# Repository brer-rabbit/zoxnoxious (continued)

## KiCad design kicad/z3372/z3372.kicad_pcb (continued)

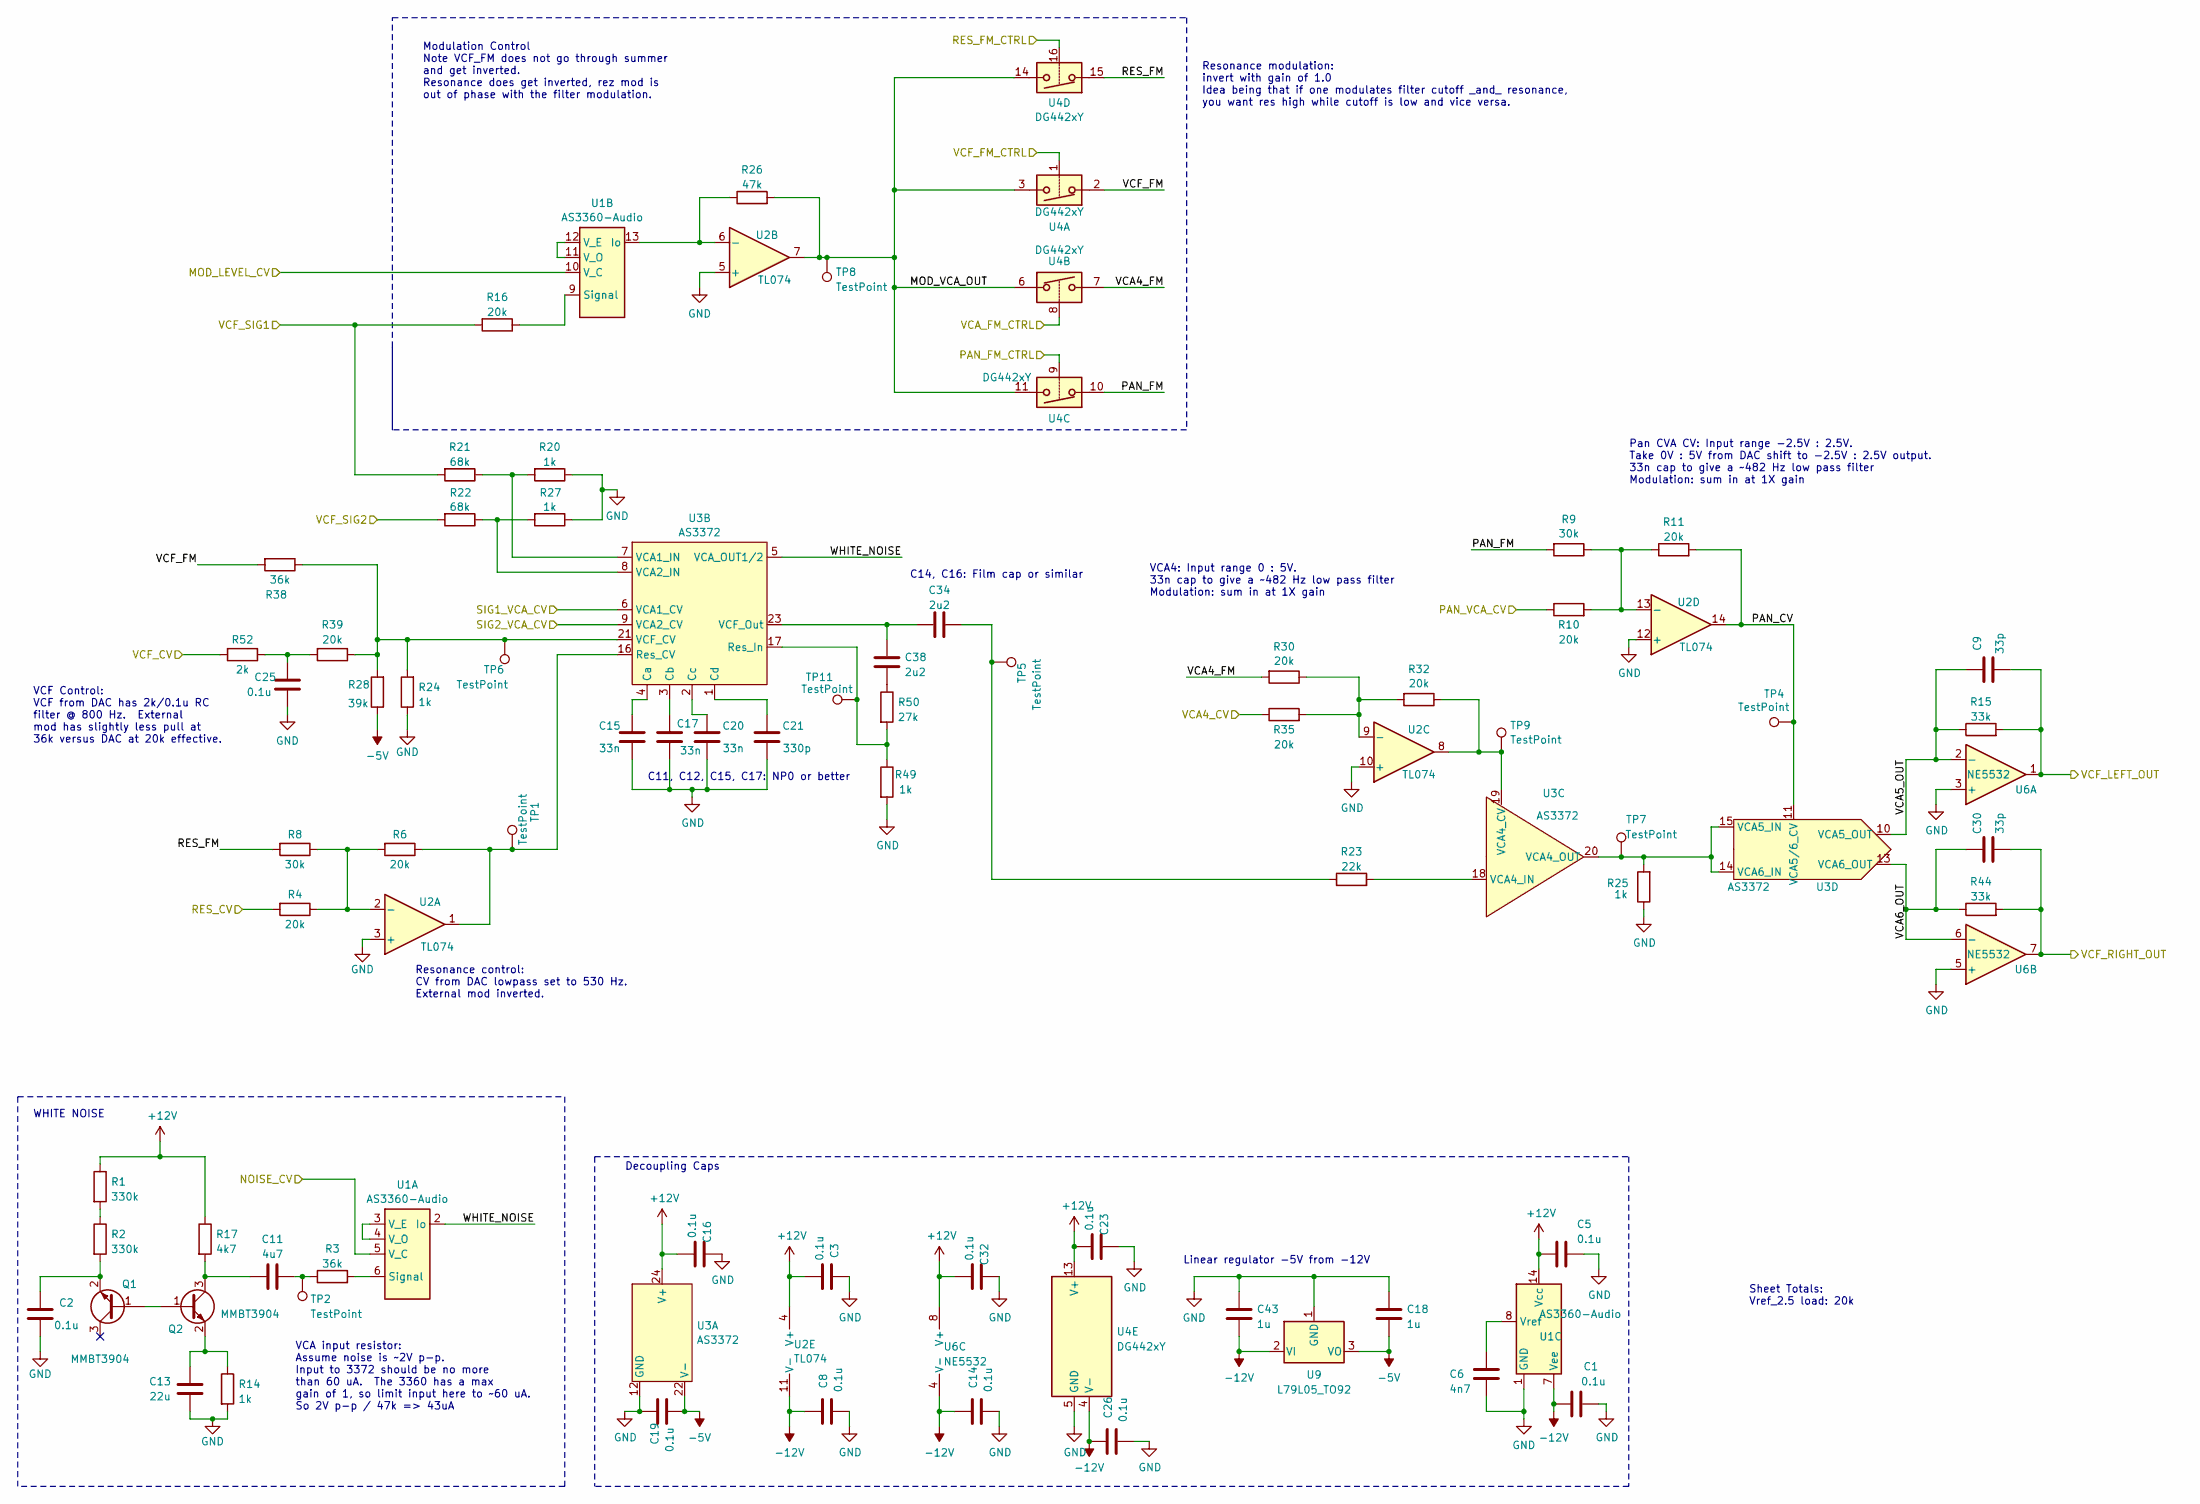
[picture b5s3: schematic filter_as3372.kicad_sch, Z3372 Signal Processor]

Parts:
C1, C2, C3, C5, C8, C14, C16, C19, C23, C25, C26, C32: 0.1u; C_0603_1608Metric; LCSC C14663
C6: 4n7; C_0603_1608Metric; LCSC C53987
C9, C30: 33p; C_0603_1608Metric; LCSC C1663
C11: 4u7; C_0805_2012Metric; LCSC C1779
C13: 22u; C_1206_3216Metric; LCSC C12891
C15, C17, C20: 33n; C_0805_2012Metric; LCSC C76628
C18, C43: 1u; C_0805_2012Metric; LCSC C28323
C21: 330p; C_0603_1608Metric; LCSC C1664
C34, C38: 2u2; C_Rect_L7.2mm_W5.5mm_P5.00mm_FKS2_FKP2_MKS2_MKP2; Digikey MKS2B042201F00KSSD
Q1, Q2: MMBT3904; SOT-23; LCSC C20526
R1, R2: 330k; R_0603_1608Metric; LCSC C23137
R3, R38: 36k; R_0603_1608Metric; LCSC C23147
R4, R6, R10, R11, R16, R30, R32, R35, R39: 20k; R_0603_1608Metric; LCSC C4184
R8, R9: 30k; R_0603_1608Metric; LCSC C22984
R14, R20, R24, R25, R27, R49: 1k; R_0603_1608Metric; LCSC C21190
R15, R44: 33k; R_0603_1608Metric; LCSC C4216
R17: 4k7; R_0603_1608Metric; LCSC C23162
R21, R22: 68k; R_0603_1608Metric; LCSC C23231
R23: 22k; R_0603_1608Metric; LCSC C31850
R26: 47k; R_0603_1608Metric; LCSC C25819
R28: 39k; R_0603_1608Metric; LCSC C23153
R50: 27k; R_0603_1608Metric; LCSC C22967
R52: 2k; R_0603_1608Metric; LCSC C22975
TP1, TP2, TP4, TP5, TP6, TP7, TP8, TP9, TP11: TestPoint; TestPoint_Pad_2.0x2.0mm
U1: AS3360-Audio; SOIC-14_3.9x8.7mm_P1.27mm
U2: TL074; TSSOP-14_4.4x5mm_P0.65mm; LCSC C96507
U3: AS3372; SOIC-24W_7.5x15.4mm_P1.27mm
U4: DG442xY; SOIC-16_3.9x9.9mm_P1.27mm; LCSC C2673321
U6: NE5532; SOIC-8_3.9x4.9mm_P1.27mm; LCSC C7426
U9: L79L05_TO92; TO-92_Inline_Wide

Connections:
+12V: C3.2, C5.2, C16.2, C23.2, C32.2, R1.1, R17.1, U1.14 (Vcc), U2.4 (V+), U3.24 (V+), U4.13 (V+), U6.8 (V+); also elsewhere on the board
-5V: C18.2, C19.2, R28.1, U3.22 (V-), U9.3 (VO)
-12V: C1.1, C8.1, C14.1, C26.1, C43.2, U1.7 (Vee), U2.11 (V-), U4.4 (V-), U6.4 (V-), U9.2 (VI); also elsewhere on the board
/DAC/FINAL_VCA4_CV: R35.1; also elsewhere on the board
/DAC/MOD_AMOUNT_CV: U1.10 (V_C); also elsewhere on the board
/DAC/NOISE_CONTROL_CV: U1.5 (V_C); also elsewhere on the board
/DAC/PAN_VCA_CV: R10.1; also elsewhere on the board
/DAC/RESONANCE_CV: R4.2; also elsewhere on the board
/DAC/SIG1_VCA1_CV: U3.6 (VCA1_CV); also elsewhere on the board
/DAC/SIG2_VCA2_CV: U3.9 (VCA2_CV); also elsewhere on the board
/DAC/VCF_CV: R52.2; also elsewhere on the board
/PAN_FM_CTRL: U4.9; also elsewhere on the board
/RES_FM_CTRL: U4.16; also elsewhere on the board
/VCA_FM_CTRL: U4.8; also elsewhere on the board
/VCF_FM_CTRL: U4.1; also elsewhere on the board
/VCF_LEFT: C9.2, R15.2, U6.1; also elsewhere on the board
/VCF_SIGNAL1: R16.2, R21.2; also elsewhere on the board
/VCF_SIGNAL2: R22.2; also elsewhere on the board
/filter_as3372/MOD_VCA_OUT: R26.2, TP8.1, U2.7, U4.3, U4.6, U4.11, U4.14
/filter_as3372/PAN_CV: R11.2, TP4.1, U2.14, U3.11 (VCA5/6_CV)
/filter_as3372/PAN_FM: R9.2, U4.10
/filter_as3372/RES_FM: R8.2, U4.15
/filter_as3372/VCA4_FM: R30.2, U4.7
/filter_as3372/VCA5_OUT: C9.1, R15.1, U3.10 (VCA5_OUT), U6.2 (-)
/filter_as3372/VCA6_OUT: C30.1, R44.1, U3.13 (VCA6_OUT), U6.6 (-)
/filter_as3372/VCF_FM: R38.2, U4.2
/filter_as3372/VCF_RIGHT_OUT: C30.2, R44.2, U6.7; also elsewhere on the board
/filter_as3372/WHITE_NOISE: U1.2 (Io), U3.5 (VCA_OUT1/2)
GND: C1.2, C2.2, C3.1, C5.1, C6.2, C8.2, C13.2, C14.2, C15.1, C16.1, C17.2, C18.1, C19.1, C20.2, C21.2, C23.1, C25.2, C26.2, C32.1, C43.1, R14.2, R20.1, R24.1, R25.1, R27.1, R49.2, U1.1 (GND), U2.3 (+), U2.5 (+), U2.10 (+), U2.12 (+), U3.12 (GND), U4.5 (GND), U6.3 (+), U6.5 (+), U9.1 (GND); also elsewhere on the board
unnamed: C11.2, R3.1, TP2.1
unnamed: C25.1, R39.2, R52.1
unnamed: C34.2, R23.1, TP5.1
unnamed: C38.2, R50.1
unnamed: Q1.1 (B), Q2.1 (B)
unnamed: C2.1, Q1.2 (E), R2.2
unnamed: C11.1, Q2.3 (C), R17.2
unnamed: C13.1, Q2.2 (E), R14.1
unnamed: R1.2, R2.1
unnamed: R3.2, U1.6 (Signal)
unnamed: U1.3 (V_E), U1.4 (V_O)
unnamed: R26.1, U1.13 (Io), U2.6 (-)
unnamed: R16.1, U1.9 (Signal)
unnamed: U1.11 (V_O), U1.12 (V_E)
unnamed: C6.1, U1.8 (Vref)
unnamed: R4.1, R6.2, R8.1, U2.2 (-)
unnamed: R30.1, R32.2, R35.2, U2.9 (-)
unnamed: R9.1, R10.2, R11.1, U2.13 (-)
unnamed: C15.2, U3.4 (Ca)
unnamed: C17.1, U3.3 (Cb)
unnamed: C20.1, U3.2 (Cc)
unnamed: C21.1, U3.1 (Cd)
unnamed: R6.1, TP1.1, U2.1, U3.16 (Res_CV)
unnamed: R49.1, R50.2, TP11.1, U3.17 (Res_In)
unnamed: R20.2, R21.1, U3.7 (VCA1_IN)
unnamed: R22.1, R27.2, U3.8 (VCA2_IN)
unnamed: R24.2, R28.2, R38.1, R39.1, TP6.1, U3.21 (VCF_CV)
unnamed: C34.1, C38.1, U3.23 (VCF_Out)
unnamed: R32.1, TP9.1, U2.8, U3.19 (VCA4_CV)
unnamed: R23.2, U3.18 (VCA4_IN)
unnamed: R25.2, TP7.1, U3.14 (VCA6_IN), U3.15 (VCA5_IN), U3.20 (VCA4_OUT)

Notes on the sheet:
Modulation Control Note VCF_FM does not go through summer and get inverted. Resonance does get inverted, rez mod is out of phase with the filter modulation.
Resonance modulation: invert with gain of 1.0 Idea being that if one modulates filter cutoff _and_ resonance, you want res high while cutoff is low and vice versa.
Resonance control: CV from DAC lowpass set to 530 Hz. External mod inverted.
VCA4: Input range 0 : 5V. 33n cap to give a ~482 Hz low pass filter Modulation: sum in at 1X gain
Decoupling Caps
C14, C16: Film cap or similar
VCF Control: VCF from DAC has 2k/0.1u RC filter @ 800 Hz. External mod has slightly less pull at 36k versus DAC at 20k effective.
WHITE NOISE
Pan CVA CV: Input range -2.5V : 2.5V. Take 0V : 5V from DAC shift to -2.5V : 2.5V output. 33n cap to give a ~482 Hz low pass filter Modulation: sum in at 1X gain
Sheet Totals: Vref_2.5 load: 20k
Linear regulator -5V from -12V
C11, C12, C15, C17: NP0 or better
VCA input resistor: Assume noise is ~2V p-p. Input to 3372 should be no more than 60 uA. The 3360 has a max gain of 1, so limit input here to ~60 uA. So 2V p-p / 47k => 43uA

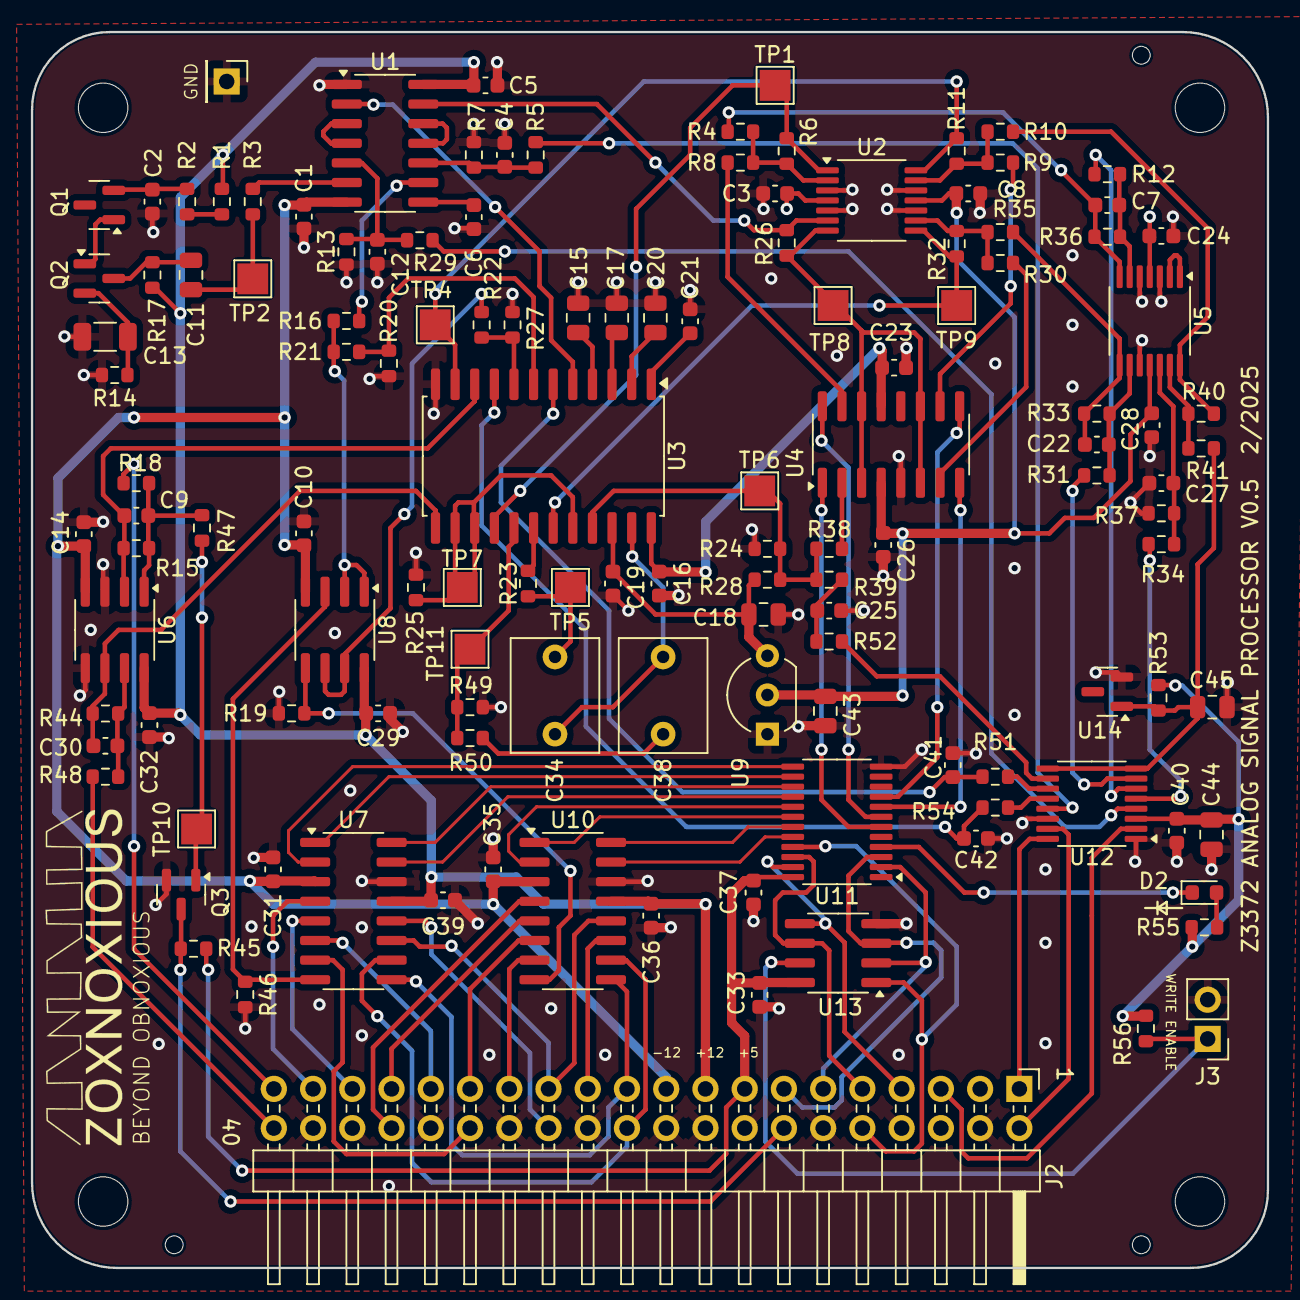
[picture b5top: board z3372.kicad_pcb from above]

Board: 4 copper layers, 80.0 x 80.0 mm, 134 parts (0 on the bottom side), 112 nets.

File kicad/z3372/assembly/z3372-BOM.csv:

Comment,Designator,Footprint,LCSC Part #
"0.1u","C1,C2,C3,C4,C5,C8,C10,C12,C14,C16,C19,C23,C24,C25,C26,C28,C29,C31,C32,C33,C35,C36,C37,C39,C40","Capacitor_SMD:C_0603_1608Metric","C14663"
"22u","C13","Capacitor_SMD:C_1206_3216Metric","C12891"
"33n","C15,C17,C20","Capacitor_SMD:C_0805_2012Metric","C76628"
"330p","C21","Capacitor_SMD:C_0603_1608Metric","C1664"
"22n","C22","Capacitor_SMD:C_0603_1608Metric","C21122"
"47n","C27","Capacitor_SMD:C_0603_1608Metric","C1622"
"4u7","C11,C44","Capacitor_SMD:C_0805_2012Metric","C1779"
"1u","C18,C43,C45","Capacitor_SMD:C_0805_2012Metric","C28323"
"4n7","C6","Capacitor_SMD:C_0603_1608Metric","C53987"
"10n","C7,C41,C42","Capacitor_SMD:C_0603_1608Metric","C57112"
"33p","C9,C30","Capacitor_SMD:C_0603_1608Metric","C1663"
"LED","D2","LED_SMD:LED_0603_1608Metric","C2286"
"MMBT3904","Q1,Q2,Q3","Package_TO_SOT_SMD:SOT-23","C20526"
"330k","R1,R2","Resistor_SMD:R_0603_1608Metric","C23137"
"47k","R12,R26","Resistor_SMD:R_0603_1608Metric","C25819"
"1k","R14,R20,R24,R25,R27,R49","Resistor_SMD:R_0603_1608Metric","C21190"
"51","R18,R48","Resistor_SMD:R_0603_1608Metric","C23197"
"100k","R19,R46,R47","Resistor_SMD:R_0603_1608Metric","C25803"
"68k","R21,R22","Resistor_SMD:R_0603_1608Metric","C23231"
"22k","R23","Resistor_SMD:R_0603_1608Metric","C31850"
"39k","R28","Resistor_SMD:R_0603_1608Metric","C23153"
"36k","R3,R38","Resistor_SMD:R_0603_1608Metric","C23147"
"20k","R4,R6,R10,R11,R16,R30,R31,R32,R33,R34,R35,R37,R39,R40,R41","Resistor_SMD:R_0603_1608Metric","C4184"
"33k","R15,R36,R44","Resistor_SMD:R_0603_1608Metric","C4216"
"10k","R45","Resistor_SMD:R_0603_1608Metric","C25804"
"15k","R5,R29,R51,R54","Resistor_SMD:R_0603_1608Metric","C22809"
"27k","R50","Resistor_SMD:R_0603_1608Metric","C22967"
"2k","R52","Resistor_SMD:R_0603_1608Metric","C22975"
"4k7","R17,R53,R55,R56","Resistor_SMD:R_0603_1608Metric","C23162"
"9k1","R7,R13","Resistor_SMD:R_0603_1608Metric","C23260"
"30k","R8,R9","Resistor_SMD:R_0603_1608Metric","C22984"
"CAT9555YI-T2","U11","Package_SO:TSSOP-24_4.4x7.8mm_P0.65mm","C83265"
"AD5328","U12","Package_SO:TSSOP-16_4.4x5mm_P0.65mm","C29162"
"M24C02-WMN","U13","Package_SO:SOIC-8_3.9x4.9mm_P1.27mm","C7562"
"LM4040AIM3-2.5","U14","Package_TO_SOT_SMD:SOT-23","C460725"
"DG442xY","U4","Package_SO:SOIC-16_3.9x9.9mm_P1.27mm","C2673321"
"TL074","U2,U5","Package_SO:TSSOP-14_4.4x5mm_P0.65mm","C96507"
"NE5532","U6","Package_SO:SOIC-8_3.9x4.9mm_P1.27mm","C7426"
"MUX508","U7,U10","Package_SO:SOIC-16_3.9x9.9mm_P1.27mm","C2673104"
"TL072","U8","Package_SO:SOIC-8_3.9x4.9mm_P1.27mm","C6961"

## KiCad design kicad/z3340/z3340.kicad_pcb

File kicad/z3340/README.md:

# Z3340 Voltage Controlled Oscillator

The Z3340 VCO is based around Alfa Rpar's AS3340 clone of the Curtis chip.  This design, like other Zoxnoxious designs, interfaces with the Zoxnoxious signal bus.

# Block Diagram

# Resources

[Datasheet](datasheet_3340.pdf)

[Kicanvas](https://kicanvas.org/?github=https%3A%2F%2Fgithub.com%2Fbrer-rabbit%2Fzoxnoxious%2Ftree%2Fmain%2Fkicad%2Fz3340)

# Demo

YouTube Demo

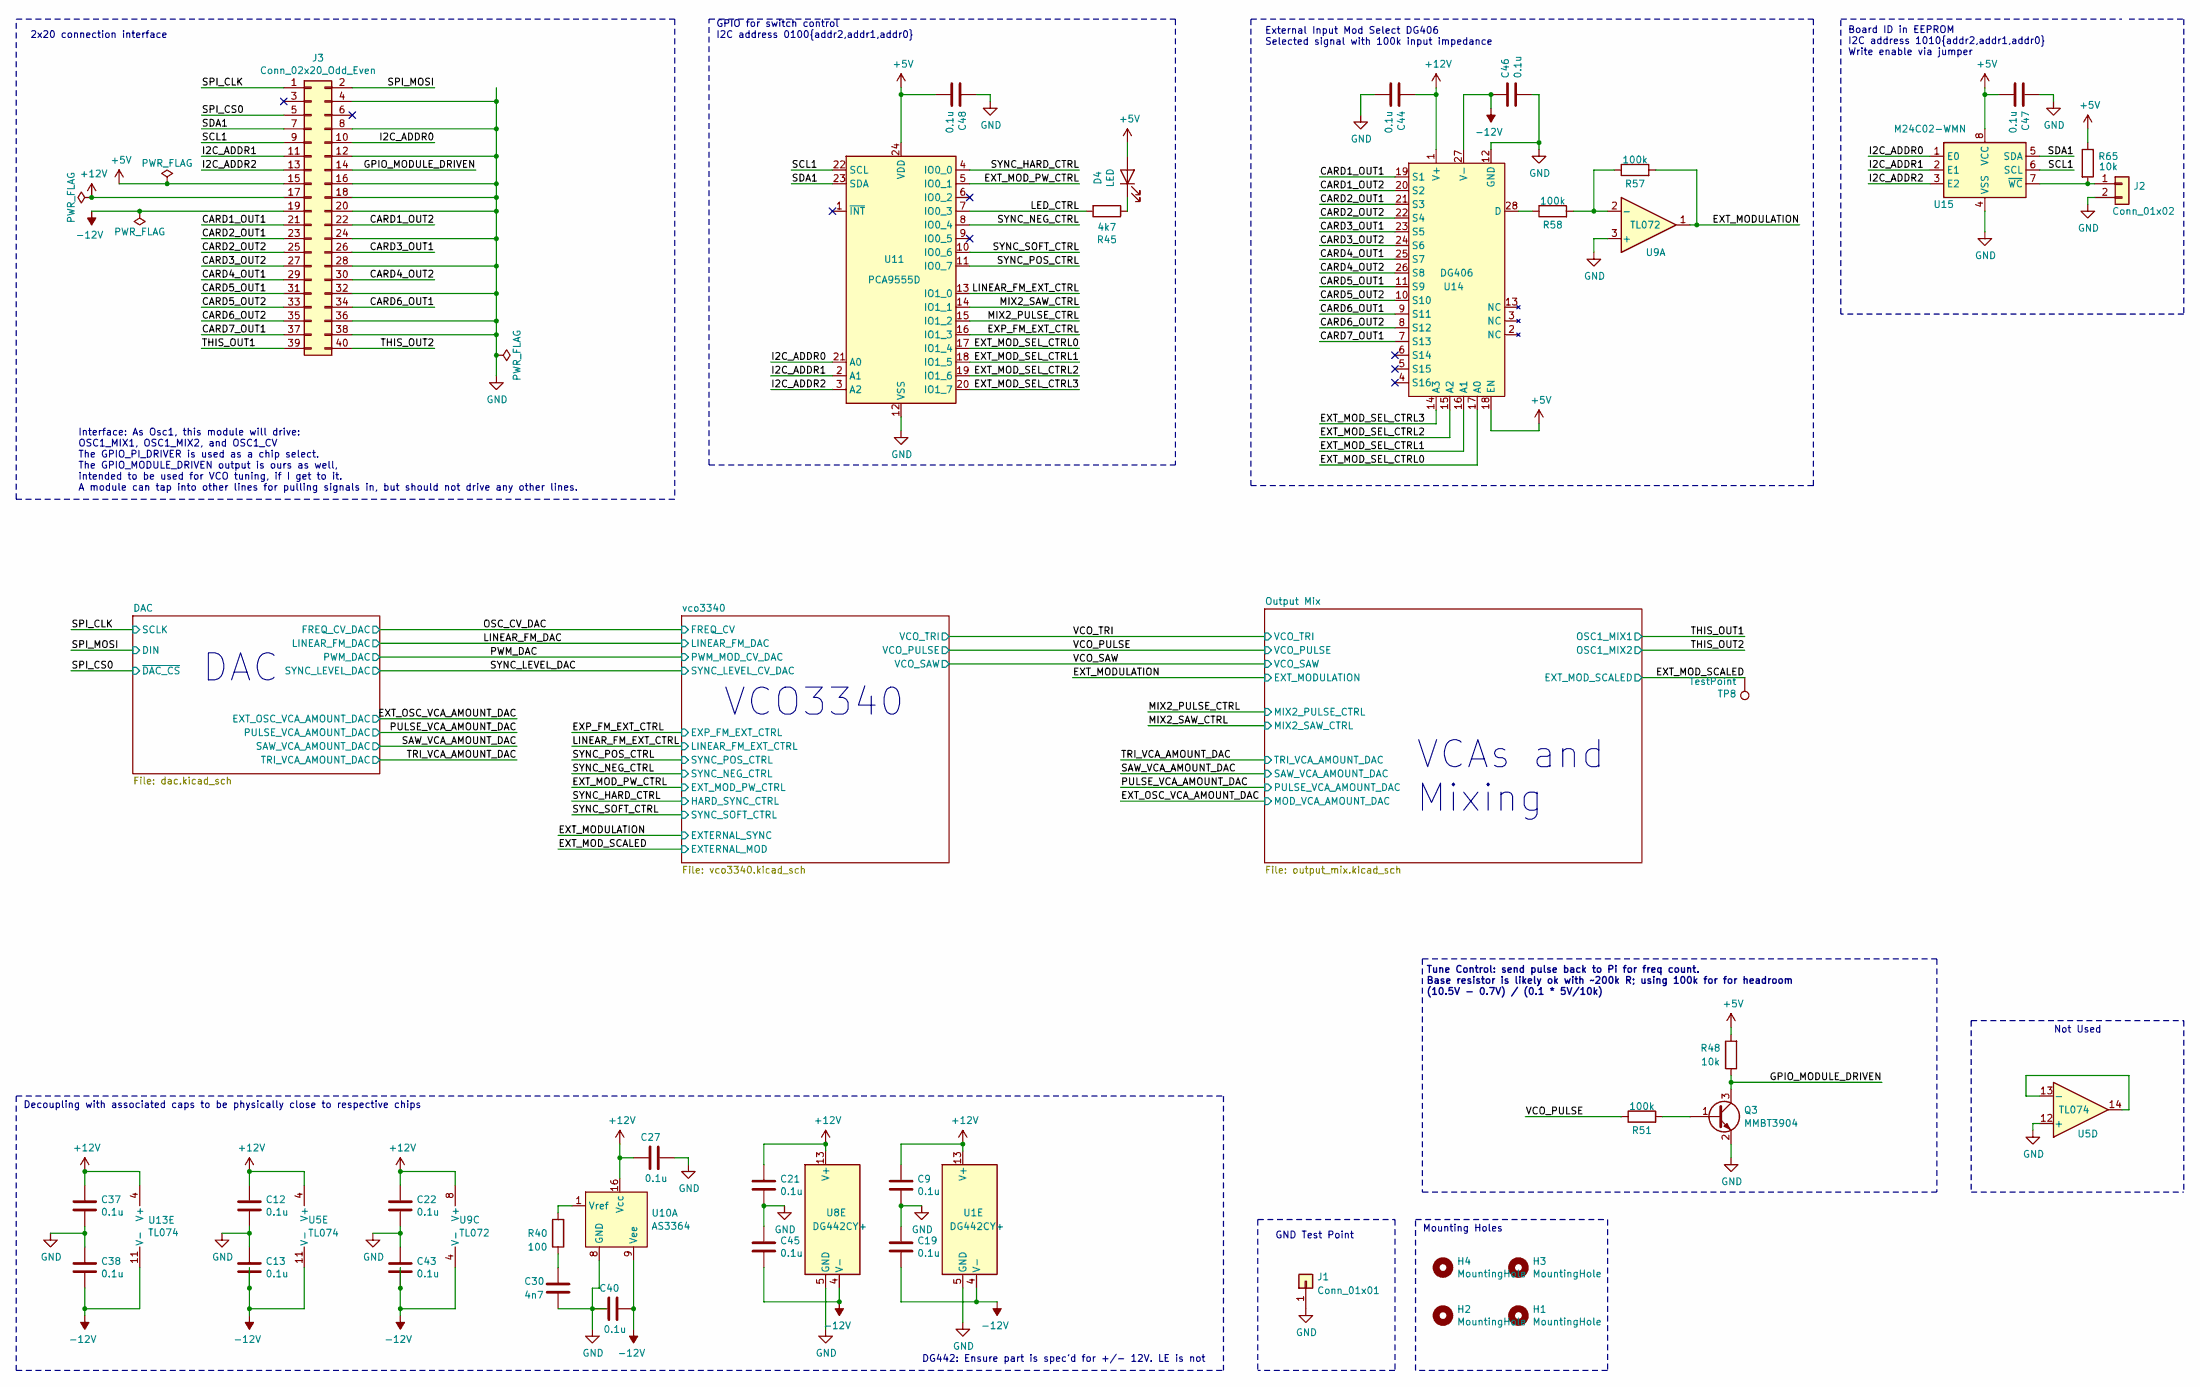
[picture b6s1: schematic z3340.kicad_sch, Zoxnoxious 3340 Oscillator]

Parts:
C9, C12, C13, C19, C21, C22, C27, C37, C38, C40, C43, C44, C45, C46, C47, C48: 0.1u; C_0603_1608Metric; LCSC C14663
C30: 4n7; C_0603_1608Metric; LCSC C53987
D4: LED; LED_0603_1608Metric; LCSC C2286
H1, H2, H3, H4: MountingHole; MountingHole_3.2mm_M3
J1: Conn_01x01; PinHeader_1x01_P2.54mm_Vertical
J2: Conn_01x02; PinHeader_1x02_P2.54mm_Vertical
J3: Conn_02x20_Odd_Even; PinHeader_2x20_P2.54mm_Horizontal
Q3: MMBT3904; SOT-23; LCSC C20526
R40: 100; R_0603_1608Metric; LCSC C22775
R45: 4k7; R_0603_1608Metric; LCSC C23162
R48, R65: 10k; R_0603_1608Metric; LCSC C25804
R51, R57, R58: 100k; R_0603_1608Metric; LCSC C25803
TP8: TestPoint; TestPoint_Pad_2.0x2.0mm; Digikey 952-2664-6-ND
U1, U8: DG442CY+; SOIC-16_3.9x9.9mm_P1.27mm; Digikey DG442CY+-ND
U5, U13: TL074; TSSOP-14_4.4x5mm_P0.65mm; LCSC C96507
U9: TL072; SSOP-8_3.9x5.05mm_P1.27mm; LCSC C6961
U10: AS3364; SOIC-16_3.9x9.9mm_P1.27mm
U11: PCA9555D; TSSOP-24_4.4x7.8mm_P0.65mm; LCSC C83265
U14: DG406; SOIC-28W_7.5x17.9mm_P1.27mm; LCSC C426318
U15: M24C02-WMN; SOIC-8_3.9x4.9mm_P1.27mm; LCSC C7562

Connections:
+5V: C47.2, C48.2, D4.2 (A), J3.15, R48.2, R65.1, U11.24 (VDD), U14.18 (EN), U15.8 (VCC); also elsewhere on the board
+12V: C9.1, C12.1, C21.1, C22.1, C27.1, C37.1, C44.1, J3.17, U1.13 (V+), U5.4 (V+), U8.13 (V+), U9.8 (V+), U10.16 (Vcc), U13.4 (V+), U14.1 (V+); also elsewhere on the board
-12V: C13.2, C19.2, C38.2, C40.2, C43.2, C45.2, C46.1, J3.19, U1.4 (V-), U5.11 (V-), U8.4 (V-), U9.4 (V-), U10.9 (Vee), U13.11 (V-), U14.27 (V-); also elsewhere on the board
/CARD1_OUT1: J3.21, U14.19 (S1)
/CARD1_OUT2: J3.22, U14.20 (S2)
/CARD2_OUT1: J3.23, U14.21 (S3)
/CARD2_OUT2: J3.25, U14.22 (S4)
/CARD3_OUT1: J3.26, U14.23 (S5)
/CARD3_OUT2: J3.27, U14.24 (S6)
/CARD4_OUT1: J3.29, U14.25 (S7)
/CARD4_OUT2: J3.30, U14.26 (S8)
/CARD5_OUT1: J3.31, U14.11 (S9)
/CARD5_OUT2: J3.33, U14.10 (S10)
/CARD6_OUT1: J3.34, U14.9 (S11)
/CARD6_OUT2: J3.35, U14.8 (S12)
/CARD7_OUT1: J3.37, U14.7 (S13)
/EXP_FM_EXT_CTRL: U11.16 (IO1_3); also elsewhere on the board
/EXT_MODULATION: R57.2, U9.1; also elsewhere on the board
/EXT_MOD_PW_CTRL: U11.5 (IO0_1); also elsewhere on the board
/EXT_MOD_SCALED: TP8.1; also elsewhere on the board
/EXT_MOD_SEL_CTRL0: U11.17 (IO1_4), U14.17 (A0)
/EXT_MOD_SEL_CTRL1: U11.18 (IO1_5), U14.16 (A1)
/EXT_MOD_SEL_CTRL2: U11.19 (IO1_6), U14.15 (A2)
/EXT_MOD_SEL_CTRL3: U11.20 (IO1_7), U14.14 (A3)
/GPIO_MODULE_DRIVEN: J3.14, Q3.3 (C), R48.1
/I2C_ADDR0: J3.10, U11.21 (A0), U15.1 (E0)
/I2C_ADDR1: J3.11, U11.2 (A1), U15.2 (E1)
/I2C_ADDR2: J3.13, U11.3 (A2), U15.3 (E2)
/LED_CTRL: R45.2, U11.7 (IO0_3)
/LINEAR_FM_EXT_CTRL: U11.13 (IO1_0); also elsewhere on the board
/MIX2_PULSE_CTRL: U11.15 (IO1_2); also elsewhere on the board
/MIX2_SAW_CTRL: U11.14 (IO1_1); also elsewhere on the board
/SCL1: J3.9, U11.22 (SCL), U15.6 (SCL)
/SDA1: J3.7, U11.23 (SDA), U15.5 (SDA)
/SPI_CLK: J3.1; also elsewhere on the board
/SPI_CS0: J3.5; also elsewhere on the board
/SPI_MOSI: J3.2; also elsewhere on the board
/SYNC_HARD_CTRL: U11.4 (IO0_0); also elsewhere on the board
/SYNC_NEG_CTRL: U11.8 (IO0_4); also elsewhere on the board
/SYNC_POS_CTRL: U11.11 (IO0_7); also elsewhere on the board
/SYNC_SOFT_CTRL: U11.10 (IO0_6); also elsewhere on the board
/THIS_OUT1: J3.39; also elsewhere on the board
/THIS_OUT2: J3.40; also elsewhere on the board
/VCO_PULSE: R51.1; also elsewhere on the board
GND: C9.2, C12.2, C13.1, C19.1, C21.2, C22.2, C27.2, C30.2, C37.2, C38.1, C40.1, C43.1, C44.2, C45.1, C46.2, C47.1, C48.1, J1.1, J2.2, J3.4, J3.8, J3.12, J3.16, J3.18, J3.20, J3.24, J3.28, J3.32, J3.36, J3.38, Q3.2 (E), U1.5 (GND), U5.12 (+), U8.5 (GND), U9.3 (+), U10.8 (GND), U11.12 (VSS), U14.12 (GND), U15.4 (VSS); also elsewhere on the board
unnamed: C30.1, R40.1
unnamed: D4.1 (K), R45.1
unnamed: J2.1, R65.2, U15.7 (~WC)
unnamed: Q3.1 (B), R51.2
unnamed: U5.13 (-), U5.14
unnamed: R57.1, R58.2, U9.2 (-)
unnamed: R40.2, U10.1 (Vref)
unnamed: R58.1, U14.28 (D)

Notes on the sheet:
Tune Control: send pulse back to Pi for freq count. Base resistor is likely ok with ~200k R; using 100k for for headroom (10.5V - 0.7V) / (0.1 * 5V/10k)
External Input Mod Select DG406 Selected signal with 100k input impedance
Decoupling with associated caps to be physically close to respective chips
DG442: Ensure part is spec’d for +/- 12V. LE is not
2x20 connection interface
VCO3340
VCAs and Mixing
GPIO for switch control I2C address 0100{addr2,addr1,addr0}
Not Used
Mounting Holes
GND Test Point
Board ID in EEPROM I2C address 1010{addr2,addr1,addr0} Write enable via jumper
Interface: As Osc1, this module will drive: OSC1_MIX1, OSC1_MIX2, and OSC1_CV The GPIO_PI_DRIVER is used as a chip select. The GPIO_MODULE_DRIVEN output is ours as well, intended to be used for VCO tuning, if I get to it. A module can tap into other lines for pulling signals in, but should not driv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
DAC

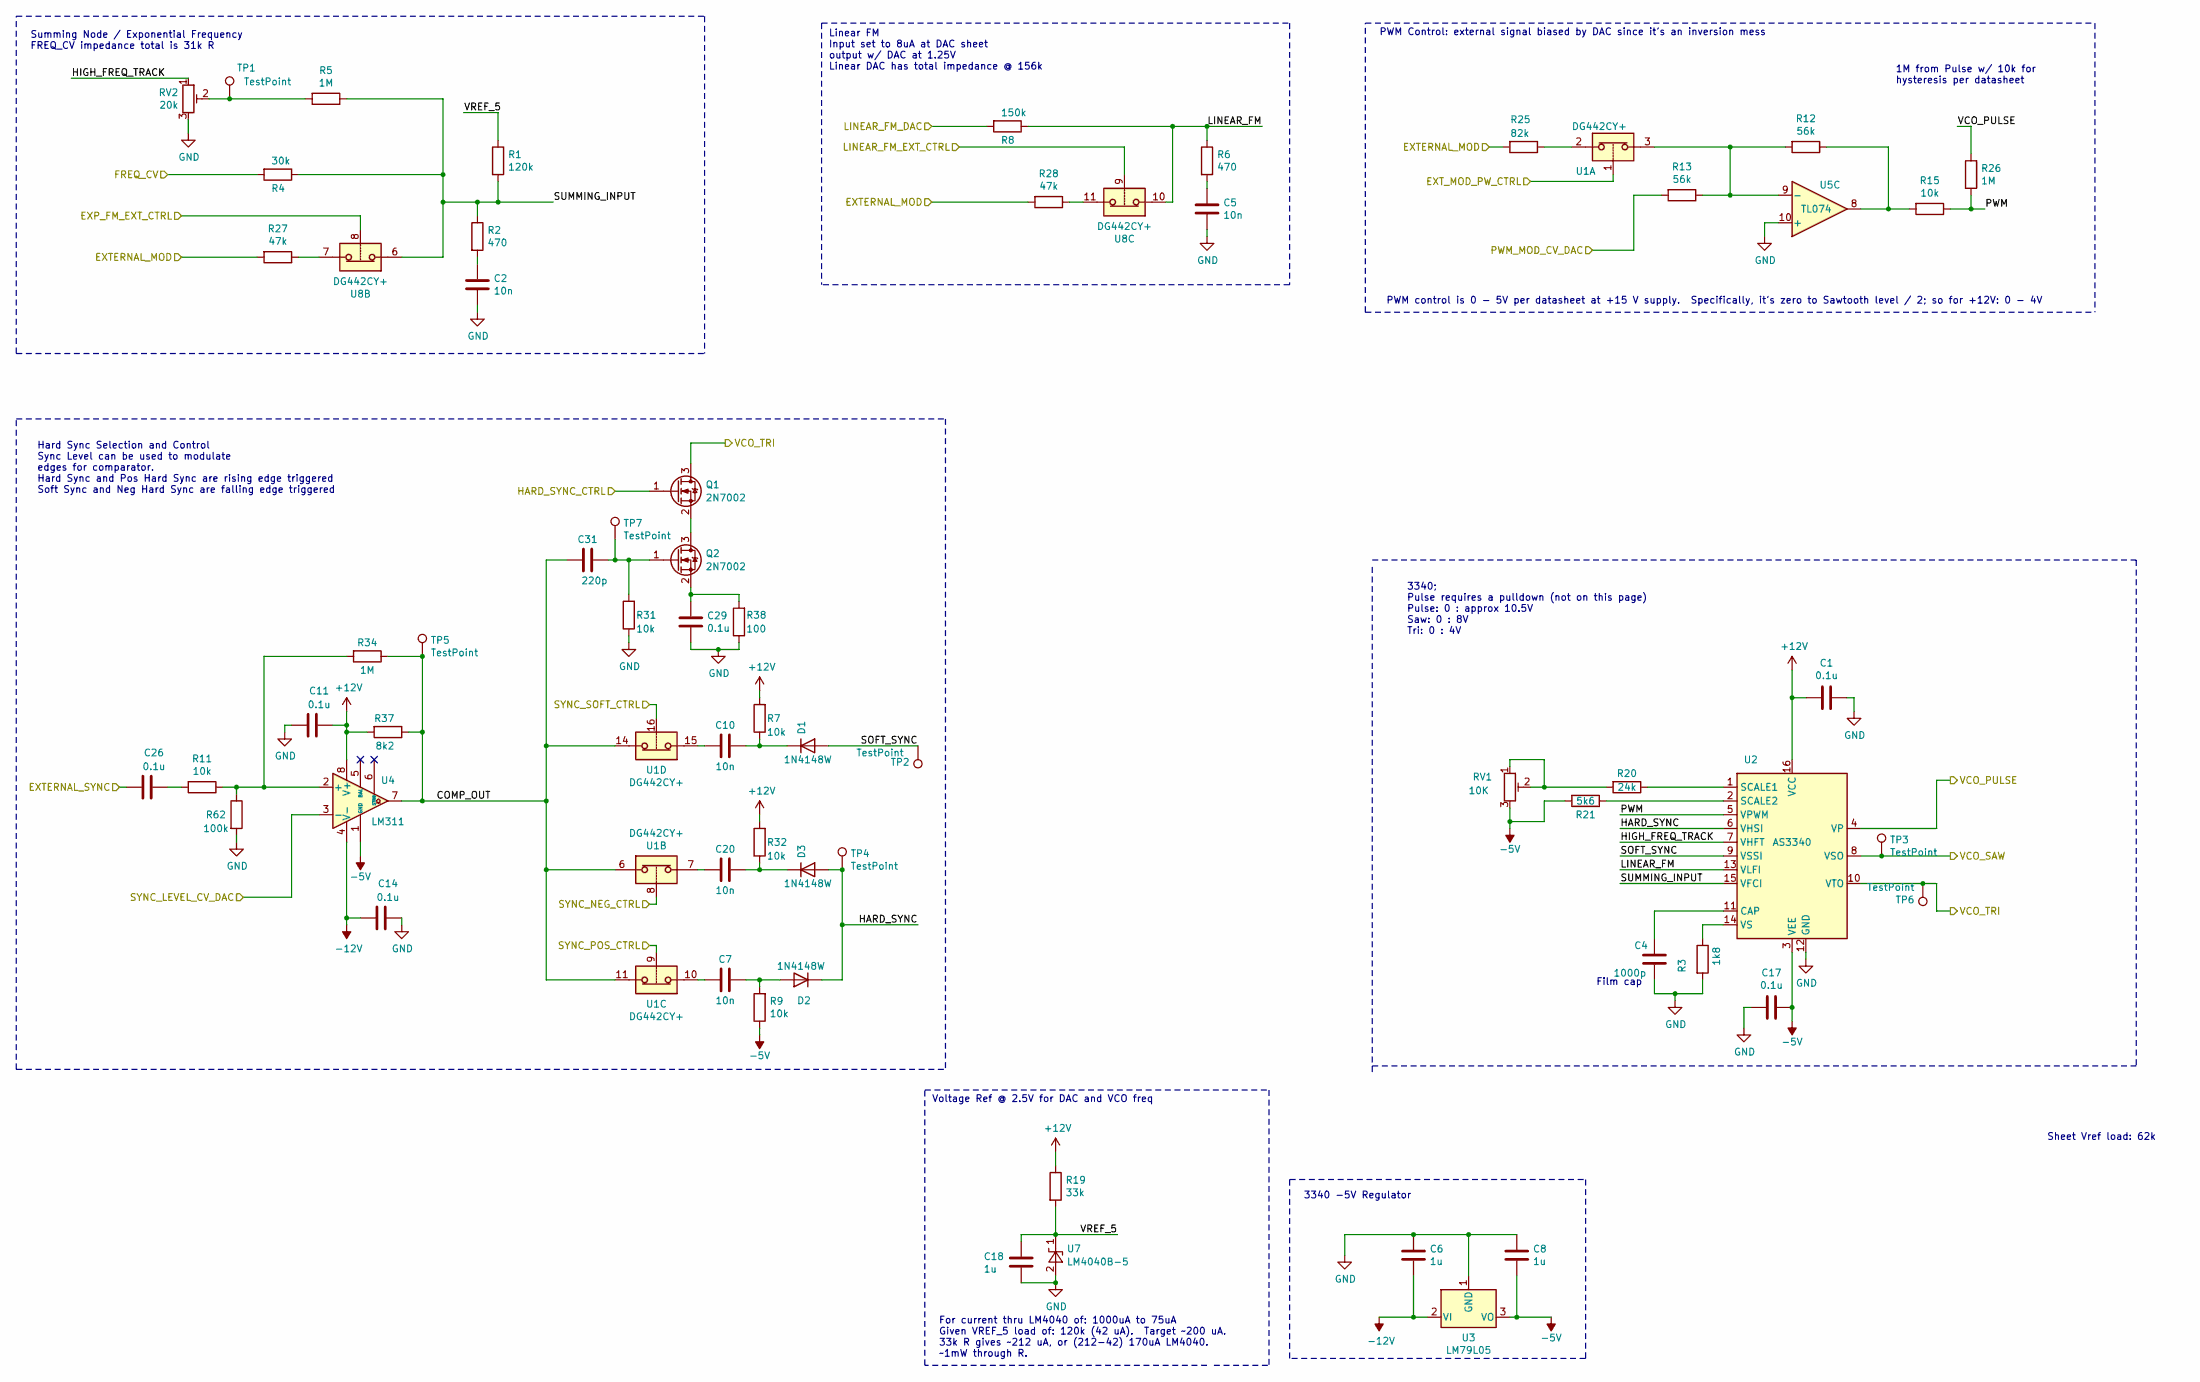
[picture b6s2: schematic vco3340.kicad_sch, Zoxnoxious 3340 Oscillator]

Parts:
C1, C11, C14, C17, C26, C29: 0.1u; C_0603_1608Metric; LCSC C14663
C2, C5, C7, C10, C20: 10n; C_0603_1608Metric; LCSC C57112
C4: 1000p; Nichicon QYX2A102KTP; Digikey QYX2A102KTP
C6, C8: 1u; C_1206_3216Metric; LCSC C1848
C18: 1u; C_0603_1608Metric; LCSC C15849
C31: 220p; C_0603_1608Metric; LCSC C1603
D1, D2, D3: 1N4148W; D_SOD-123; LCSC C81598
Q1, Q2: 2N7002; SOT-23; LCSC C8545
R1: 120k; R_0603_1608Metric; LCSC C25808
R2, R6: 470; R_0603_1608Metric; LCSC C23179
R3: 1k8; R_0603_1608Metric; LCSC C4177
R4: 30k; R_0603_1608Metric; LCSC C22984
R5, R26, R34: 1M; R_0603_1608Metric; LCSC C22935
R7, R9, R11, R15, R31, R32: 10k; R_0603_1608Metric; LCSC C25804
R8: 150k; R_0603_1608Metric; LCSC C22807
R12, R13: 56k; R_0603_1608Metric; LCSC C23206
R19: 33k; R_0603_1608Metric; LCSC C4216
R20: 24k; R_0603_1608Metric; LCSC C23352
R21: 5k6; R_0603_1608Metric; LCSC C23189
R25: 82k; R_0603_1608Metric; LCSC C23254
R27, R28: 47k; R_0603_1608Metric; LCSC C25819
R37: 8k2; R_0805_2012Metric; LCSC C17828
R38: 100; R_0603_1608Metric; LCSC C22775
R62: 100k; R_0603_1608Metric; LCSC C25803
RV1: 10K; Potentiometer_Bourns_3296W_Vertical; Digikey 490-2875-ND
RV2: 20k; Potentiometer_Bourns_3296W_Vertical; Digikey 490-2881-ND
TP1, TP2, TP3, TP4, TP5, TP6, TP7: TestPoint; TestPoint_Pad_2.0x2.0mm; Digikey 952-2664-6-ND
U1, U8: DG442CY+; SOIC-16_3.9x9.9mm_P1.27mm; Digikey DG442CY+-ND
U2: AS3340; SOIC-16_3.9x9.9mm_P1.27mm
U3: LM79L05; TO-92_Inline_Wide; Digikey 497-2960-ND
U4: LM311; SOIC-8_3.9x4.9mm_P1.27mm; LCSC C12597
U5: TL074; TSSOP-14_4.4x5mm_P0.65mm; LCSC C96507
U7: LM4040B-5; SOT-23; LCSC C69315

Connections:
+12V: C1.2, C11.1, R7.2, R19.1, R32.2, R37.2, U2.16 (VCC), U4.8 (V+); also elsewhere on the board
-5V: C8.2, C17.1, R9.1, R21.2, RV1.3, U2.3 (VEE), U3.3 (VO), U4.1 (GND)
-12V: C6.2, C14.2, U3.2 (VI), U4.4 (V-); also elsewhere on the board
/EXP_FM_EXT_CTRL: U8.8; also elsewhere on the board
/EXT_MODULATION: C26.2; also elsewhere on the board
/EXT_MOD_PW_CTRL: U1.1; also elsewhere on the board
/EXT_MOD_SCALED: R25.2, R27.2, R28.2; also elsewhere on the board
/LINEAR_FM_DAC: R8.2; also elsewhere on the board
/LINEAR_FM_EXT_CTRL: U8.9; also elsewhere on the board
/OSC_CV_DAC: R4.2; also elsewhere on the board
/PWM_DAC: R13.2; also elsewhere on the board
/SYNC_HARD_CTRL: Q1.1 (G); also elsewhere on the board
/SYNC_LEVEL_DAC: U4.3 (-); also elsewhere on the board
/SYNC_NEG_CTRL: U1.8; also elsewhere on the board
/SYNC_POS_CTRL: U1.9; also elsewhere on the board
/SYNC_SOFT_CTRL: U1.16; also elsewhere on the board
/VCO_PULSE: R26.2, U2.4 (VP); also elsewhere on the board
/VCO_SAW: TP3.1, U2.8 (VSO); also elsewhere on the board
/VCO_TRI: Q1.3 (D), TP6.1, U2.10 (VTO); also elsewhere on the board
/vco3340/COMP_OUT: C31.2, R34.1, R37.1, TP5.1, U1.6, U1.11, U1.14, U4.7
/vco3340/HARD_SYNC: D2.1 (K), D3.2 (A), TP4.1, U2.6 (VHSI)
/vco3340/HIGH_FREQ_TRACK: RV2.1, U2.7 (VHFT)
/vco3340/LINEAR_FM: R6.1, R8.1, U2.13 (VLFI), U8.10
/vco3340/PWM: R15.1, R26.1, U2.5 (VPWM)
/vco3340/SOFT_SYNC: D1.2 (A), TP2.1, U2.9 (VSSI)
/vco3340/SUMMING_INPUT: R1.2, R2.1, R4.1, R5.1, U2.15 (VFCI), U8.6
/vco3340/VREF_5: C18.1, R1.1, R19.2, U7.1 (K)
GND: C1.1, C2.2, C4.2, C5.2, C6.1, C8.1, C11.2, C14.1, C17.2, C18.2, C29.2, R3.2, R31.1, R38.1, R62.2, RV2.3, U2.12 (GND), U3.1 (GND), U5.10 (+), U7.2 (A); also elsewhere on the board
unnamed: C2.1, R2.2
unnamed: C5.1, R6.2
unnamed: C7.2, U1.10
unnamed: C10.2, U1.15
unnamed: C20.2, U1.7
unnamed: C26.1, R11.2
unnamed: C10.1, D1.1 (K), R7.1
unnamed: C7.1, D2.2 (A), R9.2
unnamed: C20.1, D3.1 (K), R32.1
unnamed: Q1.2 (S), Q2.3 (D)
unnamed: C31.1, Q2.1 (G), R31.2, TP7.1
unnamed: C29.1, Q2.2 (S), R38.2
unnamed: R5.2, RV2.2, TP1.1
unnamed: R12.1, R15.2, U5.8
unnamed: R20.2, RV1.1, RV1.2
unnamed: R25.1, U1.2
unnamed: R27.1, U8.7
unnamed: R28.1, U8.11
unnamed: C4.1, U2.11 (CAP)
unnamed: R20.1, U2.1 (SCALE1)
unnamed: R21.1, U2.2 (SCALE2)
unnamed: R3.1, U2.14 (VS)
unnamed: R11.1, R34.2, R62.1, U4.2 (+)
unnamed: R12.2, R13.1, U1.3, U5.9 (-)

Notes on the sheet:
1M from Pulse w/ 10k for hysteresis per datasheet
Hard Sync Selection and Control Sync Level can be used to modulate edges for comparator. Hard Sync and Pos Hard Sync are rising edge triggered Soft Sync and Neg Hard Sync are falling edge triggered
3340; Pulse requires a pulldown (not on this page) Pulse: 0 : approx 10.5V Saw: 0 : 8V Tri: 0 : 4V
For current thru LM4040 of: 1000uA to 75uA Given VREF_5 load of: 120k (42 uA). Target ~200 uA. 33k R gives ~212 uA, or (212-42) 170uA LM4040. ~1mW through R.
PWM Control: external signal biased by DAC since it’s an inversion mess
3340 -5V Regulator
Film cap
Linear FM Input set to 8uA at DAC sheet output w/ DAC at 1.25V Linear DAC has total impedance @ 156k
PWM control is 0 - 5V per datasheet at +15 V supply. Specifically, it’s zero to Sawtooth level / 2; so for +12V: 0 - 4V
Sheet Vref load: 62k
Voltage Ref @ 2.5V for DAC and VCO freq
Summing Node / Exponential Frequency FREQ_CV impedance total is 31k R
